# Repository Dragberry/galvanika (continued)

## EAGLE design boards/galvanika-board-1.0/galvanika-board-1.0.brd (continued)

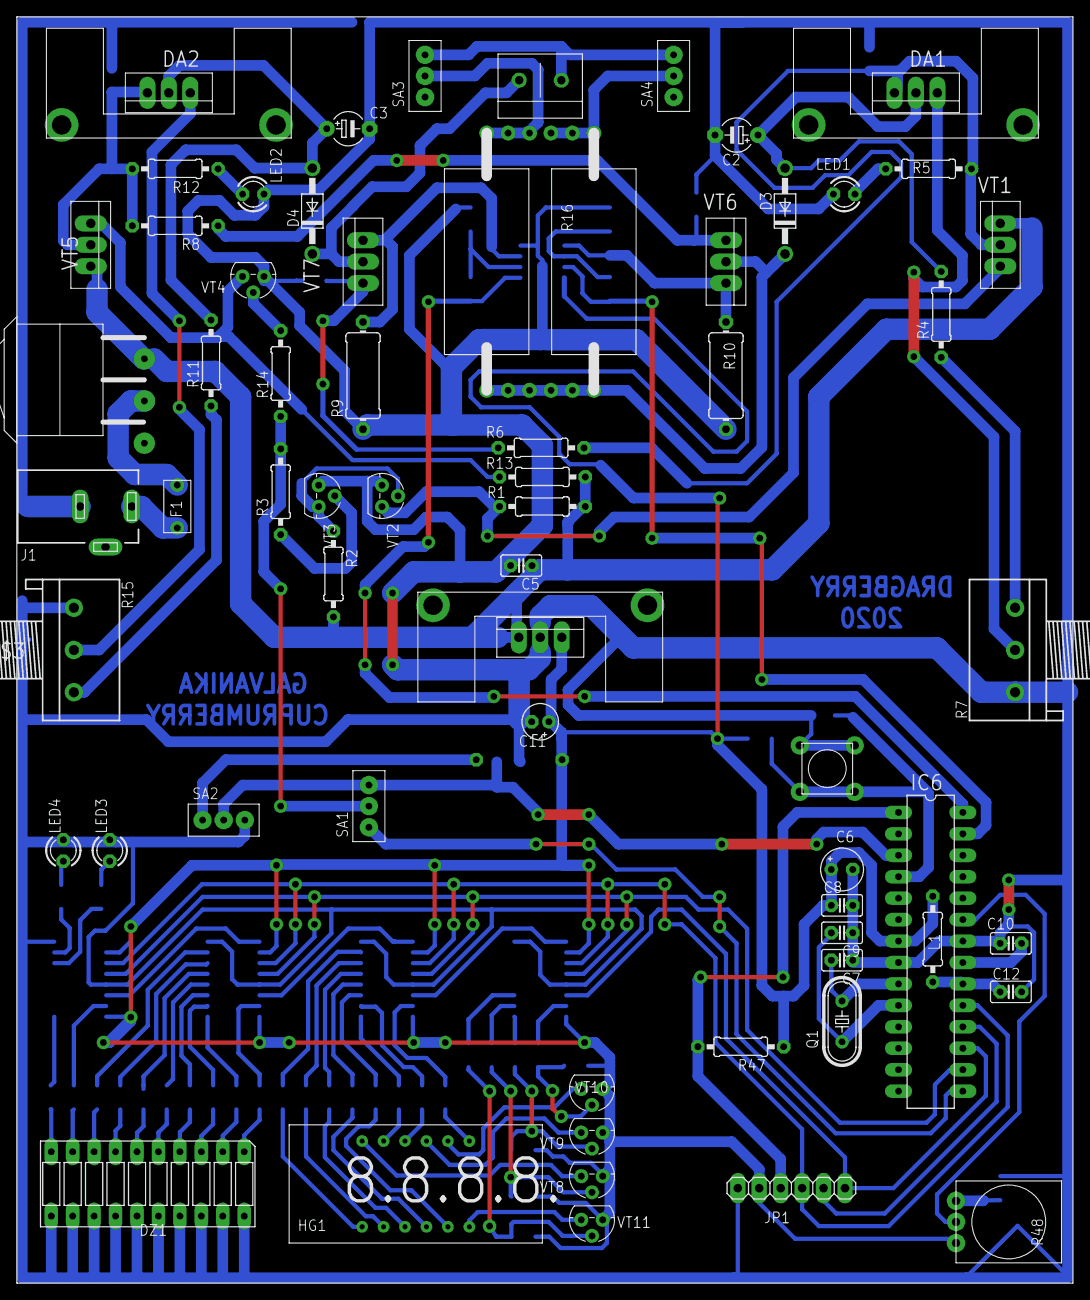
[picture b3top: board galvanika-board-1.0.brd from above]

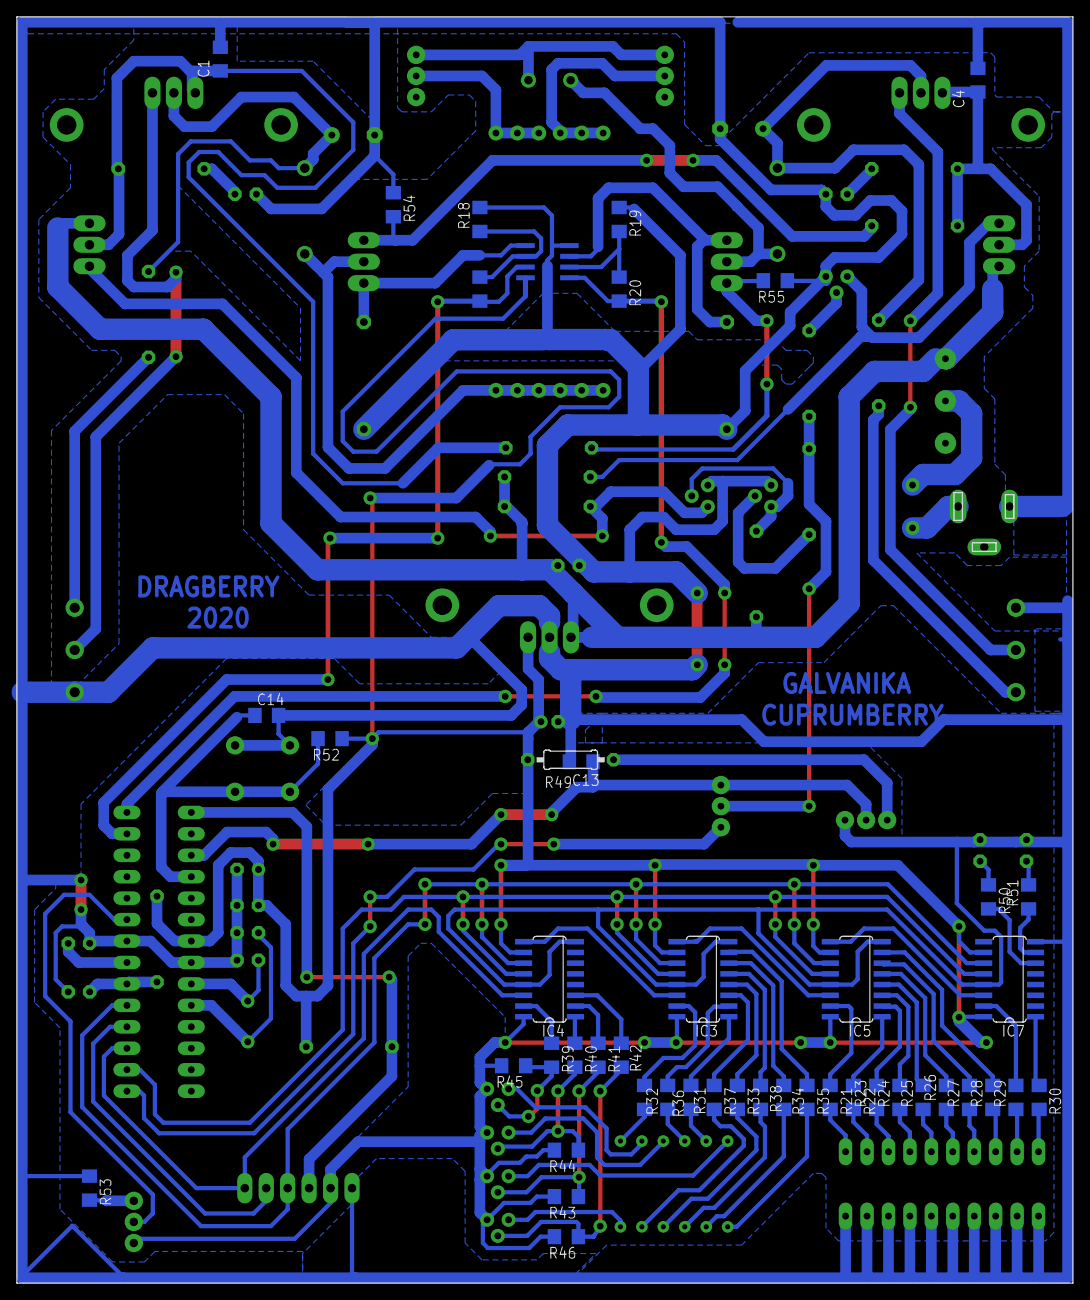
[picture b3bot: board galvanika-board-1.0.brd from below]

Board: 2 copper layers, 125.1 x 150.0 mm, 109 parts (46 on the bottom side), 104 nets.

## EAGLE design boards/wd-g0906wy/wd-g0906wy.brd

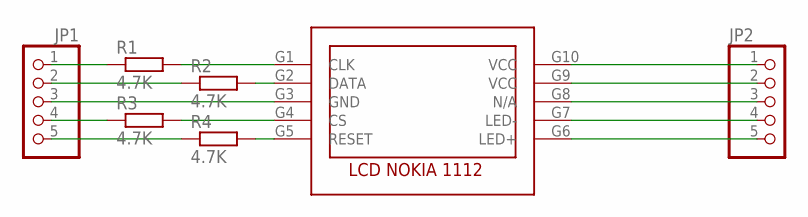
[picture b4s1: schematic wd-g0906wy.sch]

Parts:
HG1: WD-G0906WY
JP1, JP2: PINHD-1X5; 1X05
R1, R2, R3, R4: 4.7K; R1206

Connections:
unnamed: JP1.1, R1.1
unnamed: JP1.2, R2.1
unnamed: HG1.G3 (GND), JP1.3
unnamed: JP1.4, R3.1
unnamed: JP1.5, R4.1
unnamed: HG1.G9 (VCC), JP2.2
unnamed: HG1.G8 (N/A), JP2.3
unnamed: HG1.G7 (LED-), JP2.4
unnamed: HG1.G6 (LED+), JP2.5
unnamed: HG1.G1 (CLK), R1.2
unnamed: HG1.G2 (DATA), R2.2
unnamed: HG1.G4 (CS), R3.2
unnamed: HG1.G5 (RESET), R4.2
unnamed: HG1.G10 (VCC), JP2.1

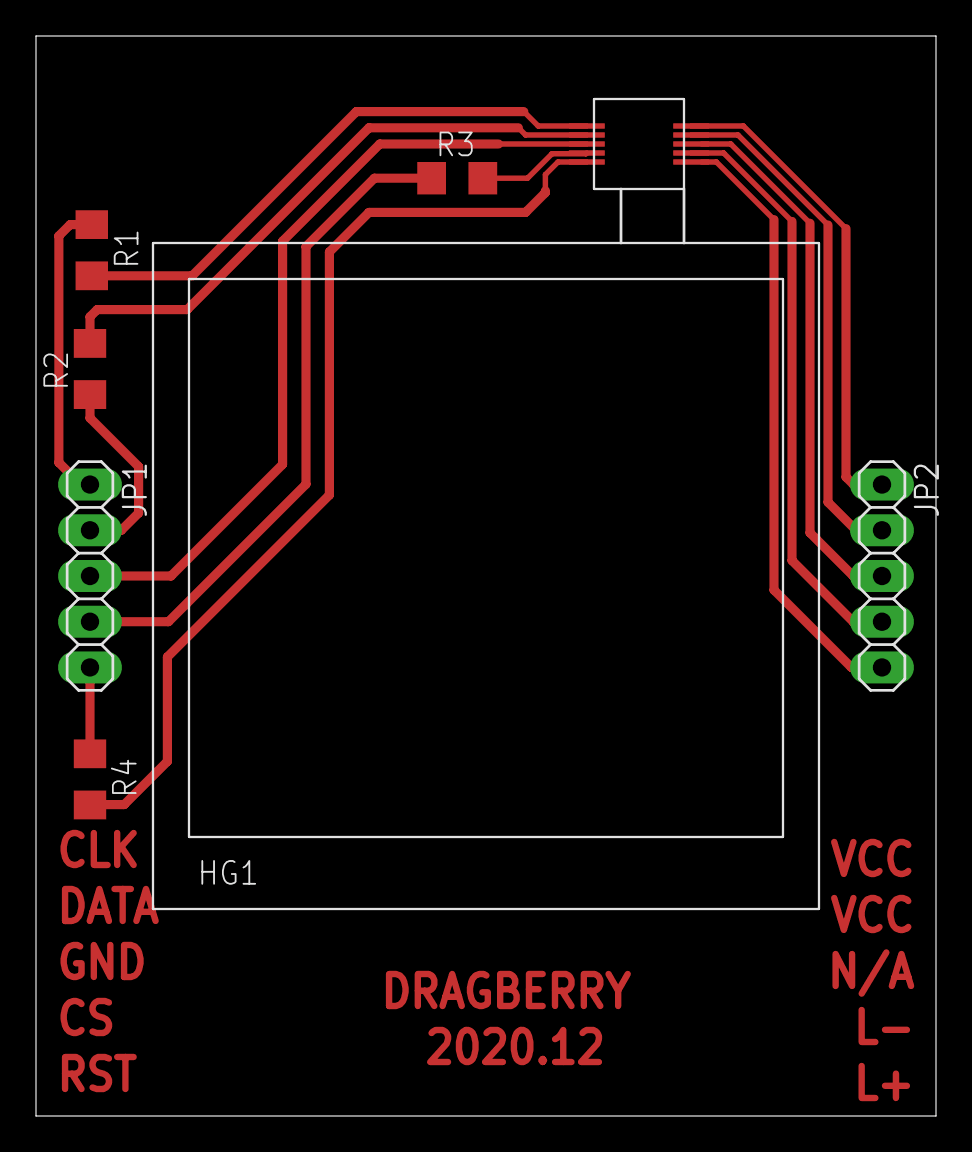
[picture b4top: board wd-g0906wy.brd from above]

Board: 2 copper layers, 50.0 x 60.0 mm, 7 parts (0 on the bottom side), 14 nets.

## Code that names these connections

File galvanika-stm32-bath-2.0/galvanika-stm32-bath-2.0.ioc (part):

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Mcu.Name=STM32F103C(8-B)Tx
Mcu.Package=LQFP48
Mcu.UserName=STM32F103C8Tx
PA0-WKUP.Signal=ADCx_IN0
PA1.Signal=ADCx_IN1
PA10.Mode=Asynchronous
PA10.Signal=USART1_RX
PA11.GPIOParameters=GPIO_PuPd
PA11.GPIO_PuPd=GPIO_PULLUP
PA11.Signal=GPIO_Input
PA12.GPIOParameters=GPIO_PuPd
PA12.GPIO_PuPd=GPIO_PULLUP
PA12.Signal=GPIO_Input
PA13.Mode=Serial_Wire
PA13.Signal=SYS_JTMS-SWDIO
PA14.Mode=Serial_Wire
PA14.Signal=SYS_JTCK-SWCLK
PA15.Signal=GPXTI15
PA2.Signal=ADCx_IN2
PA3.Signal=ADCx_IN3
PA4.Signal=ADCx_IN4
PA5.Signal=ADCx_IN5
PA6.Signal=ADCx_IN6
PA7.Signal=ADCx_IN7
PA9.Mode=Asynchronous
PA9.Signal=USART1_TX
PB0.Signal=ADCx_IN8
PB1.Signal=GPIO_Input
PB10.Signal=GPIO_Input
PB11.Signal=GPIO_Input
PB12.Signal=GPIO_Output
PB13.Signal=GPIO_Output
PB14.Signal=GPIO_Output
PB15.Signal=GPIO_Input
PB3.Signal=GPXTI3
PB4.Signal=GPXTI4
PB5.Signal=GPIO_Output
PB6.Signal=GPIO_Output
PB7.Signal=GPIO_Output
PB8.Signal=GPIO_Output
PB9.Signal=GPIO_Output
PD0-OSC_IN.Mode=HSE-External-Oscillator
PD0-OSC_IN.Signal=RCC_OSC_IN
PD1-OSC_OUT.Mode=HSE-External-Oscillator
PD1-OSC_OUT.Signal=RCC_OSC_OUT
RCC.SYSCLKFreq_VALUE=72000000
RCC.SYSCLKSource=RCC_SYSCLKSOURCE_PLLCLK
board=custom

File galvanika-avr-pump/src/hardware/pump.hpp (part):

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
    void activate_sensors()
    {
        sbi(PORTB, PB0);
        sbi(PORTD, PD5);
    }

    void deactivate_sensors()
    {
        cbi(PORTB, PB0);
        cbi(PORTD, PD5);
    }


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    void init()
    {
        // Sensor bottom output
        sbi(DDRB, PB0);
        cbi(PORTB, PB0);
        // Sensor bottom input
        cbi(DDRD, PD7);
        cbi(PORTD, PD7);
        // Sensor top output
        sbi(DDRD, PD5);
        cbi(PORTD, PD5);
        // Sensor top input
        cbi(DDRD, PD6);
        cbi(PORTD, PD6);

        sbi(DDRB, PB1);
        sbi(PORTB, PB1);

        cbi(TCCR1B, WGM13);
        sbi(TCCR1B, WGM12);
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
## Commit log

2020-07-07 'Init'
2020-07-07 schema
2020-07-08 board
2020-07-14 'board'
2020-11-08 new board version
2020-11-30 program
2020-12-14 fix direct only
2020-12-24 board v1
2021-01-06 board 2.0
2021-01-07 board v2
2021-01-23 stm32 bath 2
2021-01-25 board 2.1
2021-01-25 stm32 board v2.1
2021-02-01 pump board
2021-02-03 pump code
2021-02-06 pump
2021-02-10 galvanika board v2.2
2021-02-12 Boards v2.2
2021-02-19 Galvanika v2.2
2021-03-14 board v2.2
2021-03-16 v2.2
2021-03-17 logo
2021-03-29 Cuprumberry blog
2021-04-05 Cuprumberry blog: quick order
2021-04-07 Cuprumberry blog: seo
2021-04-10 Cuprumberry blog: mobile and normal view
2021-04-18 Cuprumberry blog: styles
2021-04-19 Cuprumberry blog: mysql
2021-04-20 Cuprumberry blog: data
2021-04-21 Cuprumberry blog: images and seo
2021-04-30 Cuprumberry blog: image carousel and data
2021-05-01 Cuprumberry blog: header
2021-05-02 Cuprumberry blog: product details
2021-05-06 Cuprumberry blog: category
2021-05-08 Cuprumberry blog: cart
2021-05-08 Bump hosted-git-info in /cuprumberry/cuprumberry/bootstrap-5.0.0-beta3
    Bumps [hosted-git-info](https://github.com/npm/hosted-git-info) from 2.8.8 to 2.8.9.
    - [Release notes](https://github.com/npm/hosted-git-info/releases)
    - [Changelog](https://github.com/npm/hosted-git-info/blob/v2.8.9/CHANGELOG.md)
    - [Commits](https://github.com/npm/hosted-git-info/compare/v2.8.8...v2.8.9)
2021-05-12 Bump postcss in /cuprumberry/cuprumberry/bootstrap-5.0.0-beta3
    Bumps [postcss](https://github.com/postcss/postcss) from 8.2.8 to 8.2.10.
    - [Release notes](https://github.com/postcss/postcss/releases)
    - [Changelog](https://github.com/postcss/postcss/blob/main/CHANGELOG.md)
    - [Commits](https://github.com/postcss/postcss/compare/8.2.8...8.2.10)
2021-05-27 Bump browserslist in /cuprumberry/cuprumberry/bootstrap-5.0.0-beta3
    Bumps [browserslist](https://github.com/browserslist/browserslist) from 4.16.3 to 4.16.6.
    - [Release notes](https://github.com/browserslist/browserslist/releases)
    - [Changelog](https://github.com/browserslist/browserslist/blob/main/CHANGELOG.md)
    - [Commits](https://github.com/browserslist/browserslist/compare/4.16.3...4.16.6)
2021-05-29 Bump ws in /cuprumberry/cuprumberry/bootstrap-5.0.0-beta3
    Bumps [ws](https://github.com/websockets/ws) from 7.4.4 to 7.4.6.
    - [Release notes](https://github.com/websockets/ws/releases)
    - [Commits](https://github.com/websockets/ws/compare/7.4.4...7.4.6)
2021-06-10 Bump trim-newlines in /cuprumberry/cuprumberry/bootstrap-5.0.0-beta3
    Bumps [trim-newlines](https://github.com/sindresorhus/trim-newlines) from 3.0.0 to 3.0.1.
    - [Release notes](https://github.com/sindresorhus/trim-newlines/releases)
    - [Commits](https://github.com/sindresorhus/trim-newlines/commits)
    ---
    updated-dependencies:
    - dependency-name: trim-newlines
2021-06-19 Cart, new products
2021-06-19 Cart, translation
2021-06-20 some changes
2021-08-13 Bump path-parse in /cuprumberry/cuprumberry/bootstrap-5.0.0-beta3
    Bumps [path-parse](https://github.com/jbgutierrez/path-parse) from 1.0.6 to 1.0.7.
    - [Release notes](https://github.com/jbgutierrez/path-parse/releases)
    - [Commits](https://github.com/jbgutierrez/path-parse/commits/v1.0.7)
    ---
    updated-dependencies:
    - dependency-name: path-parse
2021-09-22 Bump nth-check in /cuprumberry/cuprumberry/bootstrap-5.0.0-beta3
    Bumps [nth-check](https://github.com/fb55/nth-check) from 2.0.0 to 2.0.1.
    - [Release notes](https://github.com/fb55/nth-check/releases)
    - [Commits](https://github.com/fb55/nth-check/compare/v2.0.0...v2.0.1)
    ---
    updated-dependencies:
    - dependency-name: nth-check
2022-01-14 Bump engine.io in /cuprumberry/cuprumberry/bootstrap-5.0.0-beta3
    Bumps [engine.io](https://github.com/socketio/engine.io) from 4.1.1 to 4.1.2.
    - [Release notes](https://github.com/socketio/engine.io/releases)
    - [Changelog](https://github.com/socketio/engine.io/blob/4.1.2/CHANGELOG.md)
    - [Commits](https://github.com/socketio/engine.io/compare/4.1.1...4.1.2)
    ---
    updated-dependencies:
2022-01-15 Bump shelljs in /cuprumberry/cuprumberry/bootstrap-5.0.0-beta3
    Bumps [shelljs](https://github.com/shelljs/shelljs) from 0.8.4 to 0.8.5.
    - [Release notes](https://github.com/shelljs/shelljs/releases)
    - [Changelog](https://github.com/shelljs/shelljs/blob/master/CHANGELOG.md)
    - [Commits](https://github.com/shelljs/shelljs/compare/v0.8.4...v0.8.5)
    ---
    updated-dependencies:
2022-01-15 Bump follow-redirects in /cuprumberry/cuprumberry/bootstrap-5.0.0-beta3
    Bumps [follow-redirects](https://github.com/follow-redirects/follow-redirects) from 1.13.3 to 1.14.7.
    - [Release notes](https://github.com/follow-redirects/follow-redirects/releases)
    - [Commits](https://github.com/follow-redirects/follow-redirects/compare/v1.13.3...v1.14.7)
    ---
    updated-dependencies:
    - dependency-name: follow-redirects
2022-01-21 Bump log4js in /cuprumberry/cuprumberry/bootstrap-5.0.0-beta3
    Bumps [log4js](https://github.com/log4js-node/log4js-node) from 6.3.0 to 6.4.0.
    - [Release notes](https://github.com/log4js-node/log4js-node/releases)
    - [Changelog](https://github.com/log4js-node/log4js-node/blob/master/CHANGELOG.md)
    - [Commits](https://github.com/log4js-node/log4js-node/compare/v6.3.0...v6.4.0)
    ---
    updated-dependencies:
2022-01-22 Bump nanoid in /cuprumberry/cuprumberry/bootstrap-5.0.0-beta3
    Bumps [nanoid](https://github.com/ai/nanoid) from 3.1.22 to 3.2.0.
    - [Release notes](https://github.com/ai/nanoid/releases)
    - [Changelog](https://github.com/ai/nanoid/blob/main/CHANGELOG.md)
    - [Commits](https://github.com/ai/nanoid/compare/3.1.22...3.2.0)
    ---
    updated-dependencies:
2022-02-11 Bump karma in /cuprumberry/cuprumberry/bootstrap-5.0.0-beta3
    Bumps [karma](https://github.com/karma-runner/karma) from 6.2.0 to 6.3.14.
    - [Release notes](https://github.com/karma-runner/karma/releases)
    - [Changelog](https://github.com/karma-runner/karma/blob/master/CHANGELOG.md)
    - [Commits](https://github.com/karma-runner/karma/compare/v6.2.0...v6.3.14)
    ---
    updated-dependencies:
2022-02-14 Bump follow-redirects in /cuprumberry/cuprumberry/bootstrap-5.0.0-beta3
    Bumps [follow-redirects](https://github.com/follow-redirects/follow-redirects) from 1.13.3 to 1.14.8.
    - [Release notes](https://github.com/follow-redirects/follow-redirects/releases)
    - [Commits](https://github.com/follow-redirects/follow-redirects/compare/v1.13.3...v1.14.8)
    ---
    updated-dependencies:
    - dependency-name: follow-redirects
2022-03-02 Bump karma in /cuprumberry/cuprumberry/bootstrap-5.0.0-beta3
    Bumps [karma](https://github.com/karma-runner/karma) from 6.2.0 to 6.3.16.
    - [Release notes](https://github.com/karma-runner/karma/releases)
    - [Changelog](https://github.com/karma-runner/karma/blob/master/CHANGELOG.md)
    - [Commits](https://github.com/karma-runner/karma/compare/v6.2.0...v6.3.16)
    ---
    updated-dependencies:
2022-03-29 Bump minimist in /cuprumberry/cuprumberry/bootstrap-5.0.0-beta3
    Bumps [minimist](https://github.com/substack/minimist) from 1.2.5 to 1.2.6.
    - [Release notes](https://github.com/substack/minimist/releases)
    - [Commits](https://github.com/substack/minimist/compare/1.2.5...1.2.6)
    ---
    updated-dependencies:
    - dependency-name: minimist
2022-06-23 Bump shell-quote in /cuprumberry/cuprumberry/bootstrap-5.0.0-beta3
    Bumps [shell-quote](https://github.com/substack/node-shell-quote) from 1.7.2 to 1.7.3.
    - [Release notes](https://github.com/substack/node-shell-quote/releases)
    - [Changelog](https://github.com/substack/node-shell-quote/blob/master/CHANGELOG.md)
    - [Commits](https://github.com/substack/node-shell-quote/compare/v1.7.2...1.7.3)
    ---
    updated-dependencies:
2022-06-25 Bump node-fetch in /cuprumberry/cuprumberry/bootstrap-5.0.0-beta3
    Bumps [node-fetch](https://github.com/node-fetch/node-fetch) from 2.6.1 to 2.6.7.
    - [Release notes](https://github.com/node-fetch/node-fetch/releases)
    - [Commits](https://github.com/node-fetch/node-fetch/compare/v2.6.1...v2.6.7)
    ---
    updated-dependencies:
    - dependency-name: node-fetch
2022-07-20 Bump terser in /cuprumberry/cuprumberry/bootstrap-5.0.0-beta3
    Bumps [terser](https://github.com/terser/terser) from 5.1.0 to 5.14.2.
    - [Release notes](https://github.com/terser/terser/releases)
    - [Changelog](https://github.com/terser/terser/blob/master/CHANGELOG.md)
    - [Commits](https://github.com/terser/terser/commits)
    ---
    updated-dependencies:
2022-11-09 Bump socket.io-parser in /cuprumberry/cuprumberry/bootstrap-5.0.0-beta3
    Bumps [socket.io-parser](https://github.com/socketio/socket.io-parser) from 4.0.4 to 4.0.5.
    - [Release notes](https://github.com/socketio/socket.io-parser/releases)
    - [Changelog](https://github.com/socketio/socket.io-parser/blob/main/CHANGELOG.md)
    - [Commits](https://github.com/socketio/socket.io-parser/compare/4.0.4...4.0.5)
    ---
    updated-dependencies:
2022-11-11 Bump minimatch in /cuprumberry/cuprumberry/bootstrap-5.0.0-beta3
    Bumps [minimatch](https://github.com/isaacs/minimatch) from 3.0.4 to 3.1.2.
    - [Release notes](https://github.com/isaacs/minimatch/releases)
    - [Commits](https://github.com/isaacs/minimatch/compare/v3.0.4...v3.1.2)
    ---
    updated-dependencies:
    - dependency-name: minimatch
2022-12-07 Bump decode-uri-component
    Bumps [decode-uri-component](https://github.com/SamVerschueren/decode-uri-component) from 0.2.0 to 0.2.2.
    - [Release notes](https://github.com/SamVerschueren/decode-uri-component/releases)
    - [Commits](https://github.com/SamVerschueren/decode-uri-component/compare/v0.2.0...v0.2.2)
    ---
    updated-dependencies:
    - dependency-name: decode-uri-component
2022-12-08 Bump qs and body-parser
    Bumps [qs](https://github.com/ljharb/qs) and [body-parser](https://github.com/expressjs/body-parser). These dependencies needed to be updated together.
    Updates `qs` from 6.7.0 to 6.11.0
    - [Release notes](https://github.com/ljharb/qs/releases)
    - [Changelog](https://github.com/ljharb/qs/blob/main/CHANGELOG.md)
    - [Commits](https://github.com/ljharb/qs/compare/v6.7.0...v6.11.0)
    Updates `body-parser` from 1.19.0 to 1.20.1
2023-01-07 Bump json5 in /cuprumberry/cuprumberry/bootstrap-5.0.0-beta3
    Bumps [json5](https://github.com/json5/json5) from 1.0.1 to 1.0.2.
    - [Release notes](https://github.com/json5/json5/releases)
    - [Changelog](https://github.com/json5/json5/blob/main/CHANGELOG.md)
    - [Commits](https://github.com/json5/json5/compare/v1.0.1...v1.0.2)
    ---
    updated-dependencies:
